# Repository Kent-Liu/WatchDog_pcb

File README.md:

# WatchDog_pcb
一個迷你的電池電壓看門狗電路板  
A tiny WatchDog PCB for monitoring and protecting battery voltage in low-power nodes.

---

## 緣起｜Background

在 [Meshtastic Taiwan 台灣鍊網](https://www.facebook.com/groups/meshtastictw) 社群中，許多同好長期面臨太陽能節點在低電量狀態下產生的不穩定問題，例如反覆重啟、遺失設定或電池過度放電。

為了解決這類問題，社群中一位不願具名、但長期關注社群動態的熱心前輩 **Hsieh** 設計了這塊迷你電壓看門狗電路板。此設計的初衷，是在電池電壓過低時自動斷電保護節點，並在電壓恢復後重新供電，以提升整體系統的穩定性與可靠度。

本專案由發布者代為整理並開源，期望能拋磚引玉，邀請更多社群成員一同改良、延伸此設計，並將成果回饋給開源硬體社群。

---

## ♥ Thanks ♥

(原始版本) 特別感謝 **Hsieh** 無私地分享其設計，讓社群得以受益。

2026-Feb-3: 感謝熱心的 **周喬治** 大大提出的設計修改建議。

---

## 功能｜Features

- 當電池電壓低於 **3.1V** 時自動斷電保護  
- 當電池電壓回升至 **3.7V（約 50%）** 時自動恢復供電  
- 迷你尺寸設計：約 **20 mm × 10 mm**  
- 您可以變更設計透過調整電阻值，來改變斷電與恢復供電的電壓門檻  
- 設計基於 **CN312** 晶片  
  - Datasheet: https://www.shotech.de/Datasheet/consonace/DSE-CN312.pdf

---

## 使用方式｜Usage

- **IN**：連接 MPPT（太陽能充電模組）  
- **OUT**：連接節點的電池端  
- 通電前請務必再次確認 **正負極方向**

下圖為搭配 **XIAO nRF52** 節點的使用範例：

---

## 聲明與使用授權｜Disclaimer & License

### 中文說明（非法律條文）

- 本專案 **不提供任何形式的保固或維修服務**  
- 使用本設計所產生的任何風險，請使用者自行評估並承擔相關責任  
- 本專案發布者僅協助整理與開源，**並非原始設計者**，亦無法提供客製修改或設計調整之服務，敬請見諒  

---

### 授權條款｜License

本專案採用  
**CERN Open Hardware Licence Version 2 – Weakly Reciprocal (CERN-OHL-W v2)** 授權。

你可以：
- 使用、修改、打樣、製造與販售基於本設計的 PCB  
- 將本專案用於個人或商業用途  

但請注意：
- **請務必註明原作者與專案來源**  
- 若你修改了任何設計檔（包含原理圖、PCB Layout 或 KiCad 專案檔），  
  **必須以相同授權（CERN-OHL-W v2）公開釋出修改後的設計檔**  
- 在散佈或販售修改後的設計時，需一併提供對應的原始設計檔  

此授權的目的，在於確保所有改進與衍生設計能持續回饋給開源硬體社群。

---

## English Version

### Background

Within the [Meshtastic Taiwan](https://www.facebook.com/groups/meshtastictw) community, many members have long faced stability issues with solar-powered nodes when operating under low battery conditions.  
These issues commonly include repeated reboots, lost settings, or excessive battery discharge.

To address these problems, a long-time community contributor, **Hsieh** (who prefers to remain unnamed), designed this tiny battery voltage watchdog PCB.  
The original intent of this design is to automatically cut off power when the battery voltage drops too low, and to restore power once the voltage recovers, thereby improving overall system stability and reliability.

This project is published and open-sourced by the repository maintainer on behalf of the original designer.  
By sharing this design openly, we hope to encourage further improvements and extensions, and to invite the community to share their enhancements back with the open hardware ecosystem.

---

### Thanks

(Original design) Special thanks to **Hsieh** for generously sharing this design with the community.

2026-Feb-3: Special Thanks to **George Chou** for the design modification suggestions.

---

### Features

- Automatically disconnects power when battery voltage drops below **3.1V**  
- Automatically restores power when battery voltage rises above **3.7V (approximately 50%)**  
- Compact form factor: approximately **20 mm × 10 mm**  
- Voltage cutoff and restore thresholds can be adjusted by changing resistor values in your design  
- Design based on the **CN312** integrated circuit  
  - Datasheet: https://www.shotech.de/Datasheet/consonace/DSE-CN312.pdf

---

### Usage

- **IN**: Connect to MPPT (solar charging module)  
- **OUT**: Connect to the node’s battery terminal  
- Before applying power, please carefully verify correct polarity

The image below shows an example used with a **XIAO nRF52** node:

---

### Disclaimer

No warranty of any kind is provided.  
Use this design at your own risk, and assume full responsibility for any outcomes resulting from its use.

The publisher of this repository is not the original designer of the circuit and provides this project solely for the purpose of open sharing.  
No guarantees regarding performance, reliability, or suitability for any particular application are expressed or implied.

---

### License

This project is licensed under the  
**CERN Open Hardware Licence Version 2 – Weakly Reciprocal (CERN-OHL-W v2)**.

You are allowed to:
- Study, use, modify, manufacture, and sell PCBs based on this design  
- Use this project for both non-commercial and commercial purposes  

Conditions:
- **Attribution is required** — you must credit the original author and the project source  
- **If you modify any design files** (including schematics, PCB layouts, or KiCad project files),  
  you must release those modifications under the same license (**CERN-OHL-W v2**)  
- When distributing or selling modified designs, the corresponding source design files must also be made available  

This license is intended to ensure that improvements and derivative works continue to benefit the open hardware community.

**SPDX-License-Identifier:** CERN-OHL-W-2.0

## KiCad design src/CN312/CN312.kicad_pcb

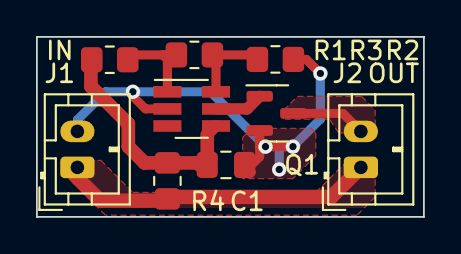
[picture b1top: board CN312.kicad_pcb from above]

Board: 2 copper layers, 21.5 x 10.0 mm, 9 parts (0 on the bottom side), 6 nets.

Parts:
C1: 1uF; C_0805_2012Metric_Pad1.18x1.45mm_HandSolder
J1: IN; JST_PH_B2B-PH-K_1x02_P2.00mm_Vertical
J2: OUT; JST_PH_B2B-PH-K_1x02_P2.00mm_Vertical
Q1: NMOS; AFP2301AS_PMOS
R1: 620k; R_0805_2012Metric_Pad1.20x1.40mm_HandSolder
R2: 330k; R_0805_2012Metric_Pad1.20x1.40mm_HandSolder
R3: 68k; R_0805_2012Metric_Pad1.20x1.40mm_HandSolder
R4: 100; R_0805_2012Metric_Pad1.20x1.40mm_HandSolder
U1: CN312; SOT-23-6_Handsoldering

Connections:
GND: C1.2, J1.2, Q1.2 (S2), R2.2, U1.2 (GND)
unnamed: J1.1, J2.1, J2.2, Q1.3 (D3), R4.1
unnamed: Q1.1 (G1), U1.5 (/LBO)
unnamed: R1.2, R3.1, U1.1 (FTH)
unnamed: R2.1, R3.2, U1.6 (RTH)
unnamed: C1.1, R1.1, R4.2, U1.4 (VCC)

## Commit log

2026-01-09 Add CERN Open Hardware Licence Version 2
    Added the CERN Open Hardware Licence Version 2 - Weakly Reciprocal to the project.
2026-01-09 Revise README with English translation and details
    Updated README to include English version and detailed project background, features, usage instructions, and licensing information.
2026-01-09 Add files via upload
    KiCad source code.
2026-02-03 Add files via upload
    PH2.0 的所在附近不要這麼大片的舖銅比較好，以防止意外造成短路。 (感謝周喬治大的貢獻)
    Reduce copper pour area near PH2.0 to prevent accidental shorts. (Thanks to George Chou)
2026-02-03 Reduce copper pour area.
    PH2.0 的所在附近不要這麼大片的舖銅比較好，以防止意外造成短路。 (感謝周喬治大的貢獻)
    Reduce copper pour area near PH2.0 to prevent accidental shorts. (Thanks to George Chou)
2026-02-03 Update thanks section with new acknowledgments
    更新周喬治大提供的修改建議。
    Update with the design modification suggestions from George Chou.
